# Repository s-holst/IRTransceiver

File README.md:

# IRTransceiver

A [Pmod](https://reference.digilentinc.com/reference/pmod/start) for emitting and receiving baseband IR signals.
It can be used to decode and emulate IR remote controls, IR communication or other IR-based sensors.

This module contains simple analog signal conditioning circuitry to connect a LED and a photodiode to FPGAs or microcontrollers.
The interface is a 12-pin Pmod (Spec B) with the following pinout:
* P1: TX, input, active high, controls the IR LED via a simple MOSFET.
* P2: GND
* P3: RX, output, is pulled high if the photodiode receives a stronger-than-average IR light.
* P4: GND
* P5, P11: GND (Pmod power supply pins)
* P6, P12: 3.3V (Pmod power supply pins)
* P7-P10: Not connected

The receiver contains a transimpedance amplifier, a high-pass filter and comparator to produce a clean digital signal.
The high-pass rejects ambient light along with signals slower than about 10 kHz, the usable bandwidth is about 100 kHz.
The receiver circuit was inspired by [IRis](https://github.com/devttys0/IRis).

## PYNQ Example Notebook

If you have a PYNQ-enabled FPGA-board, load [PYNQ_IR_Communication.ipynb](PYNQ_IR_Communication.ipynb) onto it to explore an example of sending and receiving IR signals.
This notebook works with the BaseOverlay and is completely self-contained not needing any additional drivers.
It expects an IRTransceiver connected to PMODA.

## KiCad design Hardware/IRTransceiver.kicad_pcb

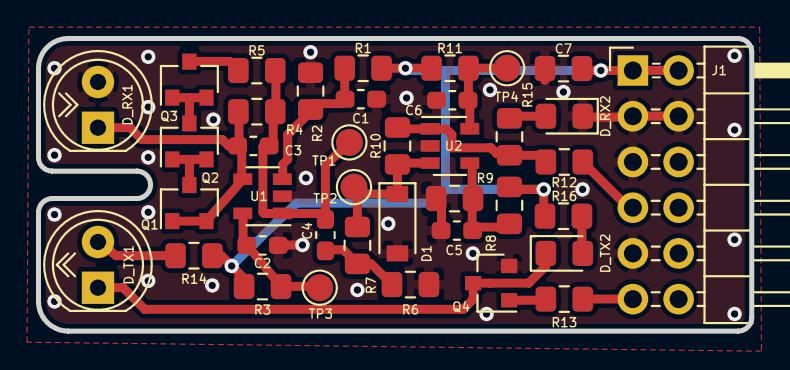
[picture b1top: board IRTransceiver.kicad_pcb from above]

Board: 2 copper layers, 39.6 x 16.3 mm, 40 parts (1 on the bottom side), 21 nets.

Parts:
C1, C2, C4, C5, C6: 100n; C_0603_1608Metric_Pad1.05x0.95mm_HandSolder
C3: 2p2; C_0603_1608Metric_Pad1.05x0.95mm_HandSolder
C7: 10u; C_0805_2012Metric_Pad1.15x1.40mm_HandSolder
D1: MBR0520; D_SOD-123
D_RX1: SFH213FA; LED_D5.0mm_IRBlack
D_RX2: LED YELLOW; LED_0805_2012Metric_Pad1.15x1.40mm_HandSolder
D_TX1: SFH4550; LED_D5.0mm_IRGrey
D_TX2: LED BL; LED_0805_2012Metric_Pad1.15x1.40mm_HandSolder
J1: Conn_02x06_Top_Bottom; PinHeader_2x06_P2.54mm_Horizontal
LOGO1: Logo_Open_Hardware_Small; OSHW-Logo_7.5x8mm_SilkScreen
Q1, Q2, Q3: MMBF4117; SOT-23
Q4: ZVN3306F; SOT-23
R1: 330k; R_0805_2012Metric_Pad1.15x1.40mm_HandSolder
R2: 22k; R_0805_2012Metric_Pad1.15x1.40mm_HandSolder
R3, R11: 10; R_0805_2012Metric_Pad1.15x1.40mm_HandSolder
R4: 1M; R_0805_2012Metric_Pad1.15x1.40mm_HandSolder
R5, R12, R13: 100; R_0805_2012Metric_Pad1.15x1.40mm_HandSolder
R6, R7: 5k6; R_0805_2012Metric_Pad1.15x1.40mm_HandSolder
R8, R10: 680k; R_0805_2012Metric_Pad1.15x1.40mm_HandSolder
R9: 10k; R_0805_2012Metric_Pad1.15x1.40mm_HandSolder
R14: 37; R_0805_2012Metric_Pad1.15x1.40mm_HandSolder
R15, R16: 2k2; R_0805_2012Metric_Pad1.15x1.40mm_HandSolder
TP1, TP2, TP3, TP4: TestPoint; TestPoint_Pad_D1.5mm
U1: TSV911ILT; SOT-23-5
U2: TLV3201; SOT-23-5

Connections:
+3V3: C7.2, J1.1, J1.2, R1.2, R3.2, R8.2, R11.2, R14.2, R16.2
/RX: J1.7, R12.2
/TX: J1.11, R13.1
GND: C1.1, C2.1, C5.2, C6.1, C7.1, D1.2, D_RX1.2, D_RX2.1, J1.3, J1.4, J1.5, J1.9, Q4.2, R2.1, R6.1, R9.1, U1.2, U2.2
unnamed: C1.2, R1.1, R2.2, U1.3
unnamed: C2.2, R3.1, TP3.1, U1.5
unnamed: C3.1, C4.2, R4.1, R5.1, TP1.1, U1.1
unnamed: C3.2, D_RX1.1, Q1.1, Q1.2, R4.2, U1.4
unnamed: C4.1, R6.2, R7.2
unnamed: C5.1, R8.1, R9.2, U2.4
unnamed: C6.2, R11.1, TP4.1, U2.5
unnamed: D1.1, R7.1, R10.1, TP2.1, U2.3
unnamed: D_RX2.2, R15.1
unnamed: D_TX1.1, D_TX2.1, Q4.3
unnamed: D_TX1.2, R14.1
unnamed: D_TX2.2, R16.1
unnamed: Q1.3, Q2.1, Q2.2
unnamed: Q2.3, Q3.1, Q3.2
unnamed: Q3.3, R5.2
unnamed: Q4.1, R13.2
unnamed: R10.2, R12.1, R15.2, U2.1

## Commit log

2020-02-06 Rev1 Design
2020-09-29 KiCad settings update (no design change)
2020-09-29 move HW to subfolder
2020-09-29 a little more info on the module
2020-10-05 Upload PYNQ example, Readme improvements

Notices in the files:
Hardware/IRTransceiver.kicad_pcb:
Copyright © 2020 Stefan Holst
Creative Commons BY-SA 4.0 International
